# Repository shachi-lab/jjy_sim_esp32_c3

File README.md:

# 📡 JJY Simulator for ESP32-C3

電波時計の補正信号をESP32-C3で自作！
NTPから取得した正確な時刻をもとに、40kHz / 60kHz のJJY信号をPWM出力で模倣する、ミニJJYシミュレーターです。

## 🛠 特徴

- ESP32-C3 + Arduino によるコンパクトな構成
- Wi-Fi設定はボタンひとつで簡単APモード
- OLEDに現在時刻を表示
- PWM出力は GPIO10 から
- JJY 40kHz（東日本）/ 60kHz（西日本）を切り替え可能
- 出力信号は基板内蔵の簡易アンテナから放射

<br/>

## ⚙️ 使用方法

### 1. コンパイル・書き込み

1. Arduino IDE で ESP32ボードを有効にする  
   - ボードマネージャURL：`https://dl.espressif.com/dl/package_esp32_index.json`
   - 対象ボード：**ESP32-C3 Dev Module**

2. 必要なライブラリをインストールする  
   - [WiFiManager](https://github.com/tzapu/WiFiManager)（バージョン 2.0.17 推奨）
   - [ESP8266 and ESP32 OLED driver for SSD1306 displays](https://github.com/ThingPulse/esp8266-oled-ssd1306)（バージョン 4.6.0 推奨）

   ※ Arduino IDE の「ライブラリを管理」メニューからインストール可能です。

3. `JJY_Sim_ESP32_C3.ino` を開き、必要に応じて以下を編集：
   - `#define JJY_TYPE 0` → `0: 40kHz`, `1: 60kHz`

4. 書き込みポートとボード設定を確認して、コンパイル＆アップロード

> 💡 補足：
> ESP32-C3は、外付けのUSBシリアルICを使わず、チップ内蔵の**ネイティブUSB-UART**機能で書き込み・シリアル通信を行います。
> 一部の環境（特にWindows）では、デバイス認識のために**Espressif提供のUSBドライバ**が必要になる場合があります。

- ドライバDLページ 👉 https://www.espressif.com/en/support/download/other-tools

>⚠️ 初回起動について
> プログラムを書き込んだ直後の「初回起動」では、内部FLASHにファイルシステムを構築する処理が行われます。  
> このため、数十秒ほど反応がなく「ハングしたように見える」場合があります。  
> 完了すると自動的に再起動し、以降は通常通りすぐに動作しますが、再起動しない場合は、RESETボタンでリセットしてください。

### 2. Wi-Fi設定

- 電源投入 or リセット後、5秒以内に CONFIGスイッチを押す
- `ESP32_XXXXXXXX` というAPが起動（パスキー：`password`）
- スマホやPCから接続 → キャプティブポータルでSSID/パスキーを設定

### 3. 動作確認

- 電源投入 or リセット後、5秒間放置すると、WiFiのAPに接続しに行きます。
- APに接続すると、NTPサーバーから時刻を取得します。
- OLEDに現在時刻が表示され、0秒からPWMでJJY信号出力開始
- 電波時計の「受信ボタン」を押して、近くに置いておくだけ！

## 🔌 ピンアサイン（主なもの）

| 機能 | GPIO | 備考 |
|------|------|------|
| JJY PWM出力 | 10 | 変調された信号を出力 |
| CONFIGスイッチ | 9 | Wi-Fi設定用（**BOOTピンと兼用**） |
| ACT LED | 5 | 動作中LED |
| IND LED | 0 | 状態表示用LED（共用可） |
| OLED Reset | 2 | OLEDモジュールリセット |
| OLED SDA|7| OLED I2C データー|
| OLED SCL |6|OLED I2C クロック|

## 🧾 ファイル構成

```
JJY_Sim_ESP32_C3.ino       // メインスケッチ
wire_compat.h              // ESP32-C3 用の I2C バス互換ヘッダ
```

## 📎 依存ライブラリ

- [WiFiManager](https://github.com/tzapu/WiFiManager)
- [ESP8266 and ESP32 OLED driver](https://github.com/ThingPulse/esp8266-oled-ssd1306)

## 🔗 関連リンク

- ブログ記事（詳細解説＋ケースや基板配布）  
  👉 https://blog.shachi-lab.com/033_jjy_simulator/

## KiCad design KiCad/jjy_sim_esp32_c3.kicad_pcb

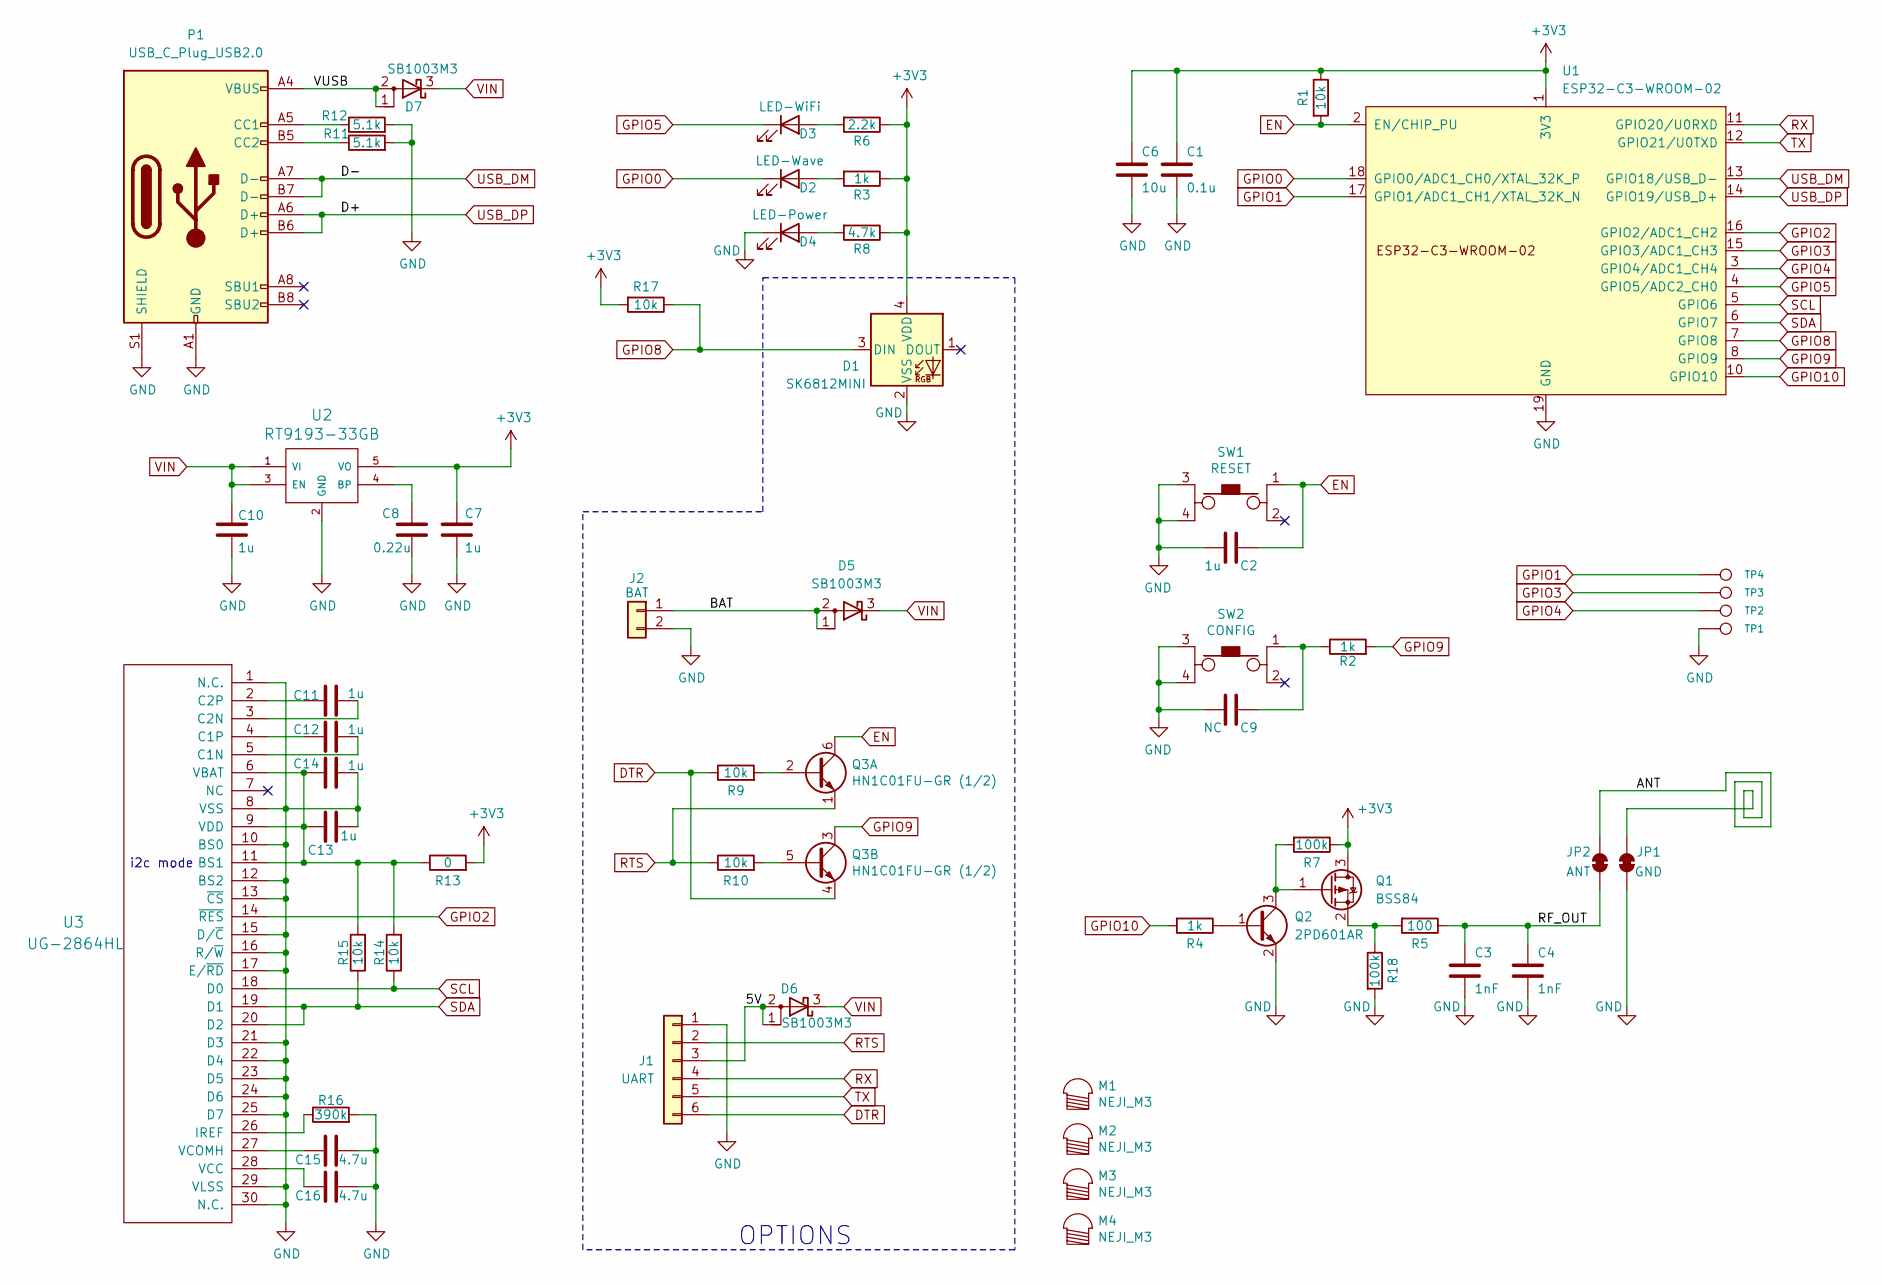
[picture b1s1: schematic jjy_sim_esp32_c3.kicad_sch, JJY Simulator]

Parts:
C1: 0.1u; C_0603_1608Metric
C2, C7, C10, C11, C12, C13, C14: 1u; C_0603_1608Metric
C3, C4: 1nF; C_0603_1608Metric
C6: 10u; C_0603_1608Metric
C8: 0.22u; C_0603_1608Metric
C9: NC; C_0603_1608Metric
C15, C16: 4.7u; C_0603_1608Metric
D1: SK6812MINI; LED_SK6812MINI_PLCC4_3.5x3.5mm_P1.75mm
D2: LED-Wave; LED_0603_1608Metric
D3: LED-WiFi; LED_0603_1608Metric
D4: LED-Power; LED_0603_1608Metric
D5, D6, D7: SB1003M3; SOT-323_SC-70
J1: UART; PinHeader_1x06_P2.54mm_Horizontal
J2: BAT; JST_PH_B2B-PH-K_1x02_P2.00mm_Vertical
JP1: GND; Jumper-2_TH_3.81mm
JP2: ANT; Jumper-2_TH_3.81mm
M1, M2, M3, M4: NEJI_M3; HOLE-3M_55
P1: USB_C_Plug_USB2.0; 5077CR-16SMC2-BK-TR
Q1: BSS84; SOT-23
Q2: 2PD601AR; SC-59
Q3: HN1C01FU-GR (1/2); 2-2J1A
R1, R9, R10, R14, R15, R17: 10k; R_0603_1608Metric
R2, R3, R4: 1k; R_0603_1608Metric
R5: 100; R_0603_1608Metric
R6: 2.2k; R_0603_1608Metric
R7, R18: 100k; R_0603_1608Metric
R8: 4.7k; R_0603_1608Metric
R11, R12: 5.1k; R_0603_1608Metric
R13: 0; R_0603_1608Metric
R16: 390k; R_0603_1608Metric
SW1: RESET; SKRPACE010
SW2: CONFIG; SKRPACE010
TP1, TP2, TP3, TP4: TP; TestPoint_THTPad_D1.5mm_Drill0.7mm
U1: ESP32-C3-WROOM-02
U2: RT9193-33GB; SOT-23-5
U3: UG-2864HL; UG-2864-FPC

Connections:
+3V3: C1.1, C6.1, C7.1, D1.4 (VDD), Q1.3 (D), R1.1, R3.1, R6.1, R7.1, R8.1, R13.2, R17.2, U1.1 (3V3), U2.5 (VO)
/5V: D6.1 (A), D6.2 (A), J1.3
/ANT: JP1.2 (B), JP2.2 (B)
/BAT: D5.1 (A), D5.2 (A), J2.1
/RF_OUT: C3.1, C4.1, JP2.1 (A), R5.1
/VUSB: D7.1 (A), D7.2 (A), P1.A4 (VBUS), P1.A9 (VBUS), P1.B4 (VBUS), P1.B9 (VBUS)
DTR: J1.6, Q3.4 (E2), R9.1
EN: C2.2, Q3.6 (C1), R1.2, SW1.1, U1.2 (EN/CHIP_PU)
GND: C1.2, C2.1, C3.2, C4.2, C6.2, C7.2, C8.2, C9.1, C10.2, C13.2, C14.2, C15.2, C16.2, D1.2 (VSS), D4.1 (K), J1.1, J2.2, JP1.1 (A), P1.A1 (GND), P1.A12 (GND), P1.B1 (GND), P1.B12 (GND), P1.S1 (SHIELD), Q2.2 (E), R11.2, R12.2, R16.2, R18.2, SW1.3, SW1.4, SW2.3, SW2.4, TP1.1, U1.9 (GND), U1.19 (GND), U2.2 (GND), U3.1 (N.C.), U3.8 (VSS), U3.10 (BS0), U3.12 (BS2), U3.13 (~CS), U3.15 (D/~C), U3.16 (R/~W), U3.17 (E/~RD), U3.21 (D3), U3.22 (D4), U3.23 (D5), U3.24 (D6), U3.25 (D7), U3.29 (VLSS), U3.30 (N.C.)
GPIO0: D2.1 (K), U1.18 (GPIO0/ADC1_CH0/XTAL_32K_P)
GPIO1: TP4.1, U1.17 (GPIO1/ADC1_CH1/XTAL_32K_N)
GPIO2: U1.16 (GPIO2/ADC1_CH2), U3.14 (~RES)
GPIO3: TP3.1, U1.15 (GPIO3/ADC1_CH3)
GPIO4: TP2.1, U1.3 (GPIO4/ADC1_CH4)
GPIO5: D3.1 (K), U1.4 (GPIO5/ADC2_CH0)
GPIO8: D1.3 (DIN), R17.1, U1.7 (GPIO8)
GPIO9: Q3.3 (C2), R2.2, U1.8 (GPIO9)
GPIO10: R4.2, U1.10 (GPIO10)
unnamed: C9.2, R2.1, SW2.1
unnamed: D2.2 (A), R3.2
unnamed: D3.2 (A), R6.2
unnamed: D4.2 (A), R8.2
unnamed: P1.A5 (CC1), R12.1
unnamed: P1.B5 (CC2), R11.1
unnamed: Q1.1 (G), Q2.3 (C), R7.2
unnamed: Q1.2 (S), R5.2, R18.1
unnamed: Q2.1 (B), R4.1
unnamed: Q3.2 (B1), R9.2
unnamed: Q3.5 (B2), R10.2
unnamed: C8.1, U2.4 (BP)
unnamed: C13.1, C14.1, R13.1, R14.2, R15.2, U3.6 (VBAT), U3.9 (VDD), U3.11 (BS1)
unnamed: C12.2, U3.5 (C1N)
unnamed: C12.1, U3.4 (C1P)
unnamed: C11.2, U3.3 (C2N)
unnamed: C11.1, U3.2 (C2P)
unnamed: R16.1, U3.26 (IREF)
unnamed: C16.1, U3.28 (VCC)
unnamed: C15.1, U3.27 (VCOMH)
RTS: J1.2, Q3.1 (E1), R10.1
RX: J1.4, U1.11 (GPIO20/U0RXD)
SCL: R14.1, U1.5 (GPIO6), U3.18 (D0)
SDA: R15.1, U1.6 (GPIO7), U3.19 (D1), U3.20 (D2)
TX: J1.5, U1.12 (GPIO21/U0TXD)
USB_DM: P1.A7 (D-), P1.B7 (D-), U1.13 (GPIO18/USB_D-)
USB_DP: P1.A6 (D+), P1.B6 (D+), U1.14 (GPIO19/USB_D+)
VIN: C10.1, D5.3 (K), D6.3 (K), D7.3 (K), U2.1 (VI), U2.3 (EN)

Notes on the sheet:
OPTIONS
i2c mode

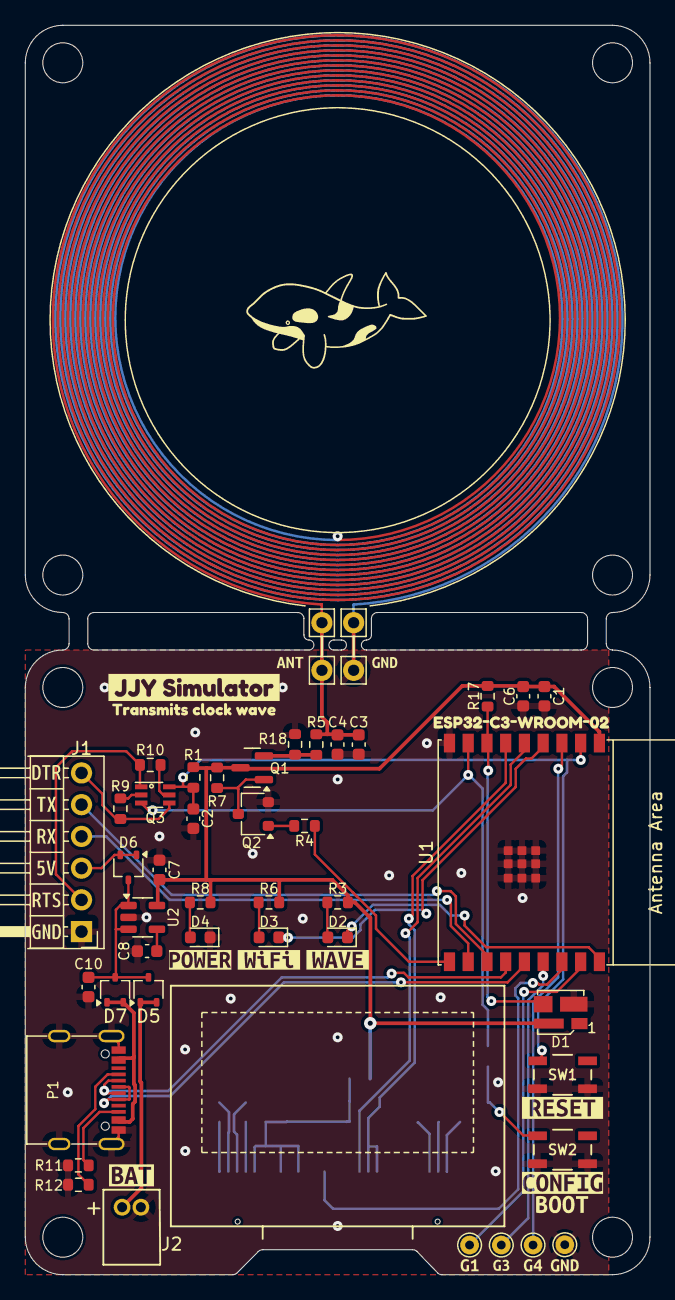
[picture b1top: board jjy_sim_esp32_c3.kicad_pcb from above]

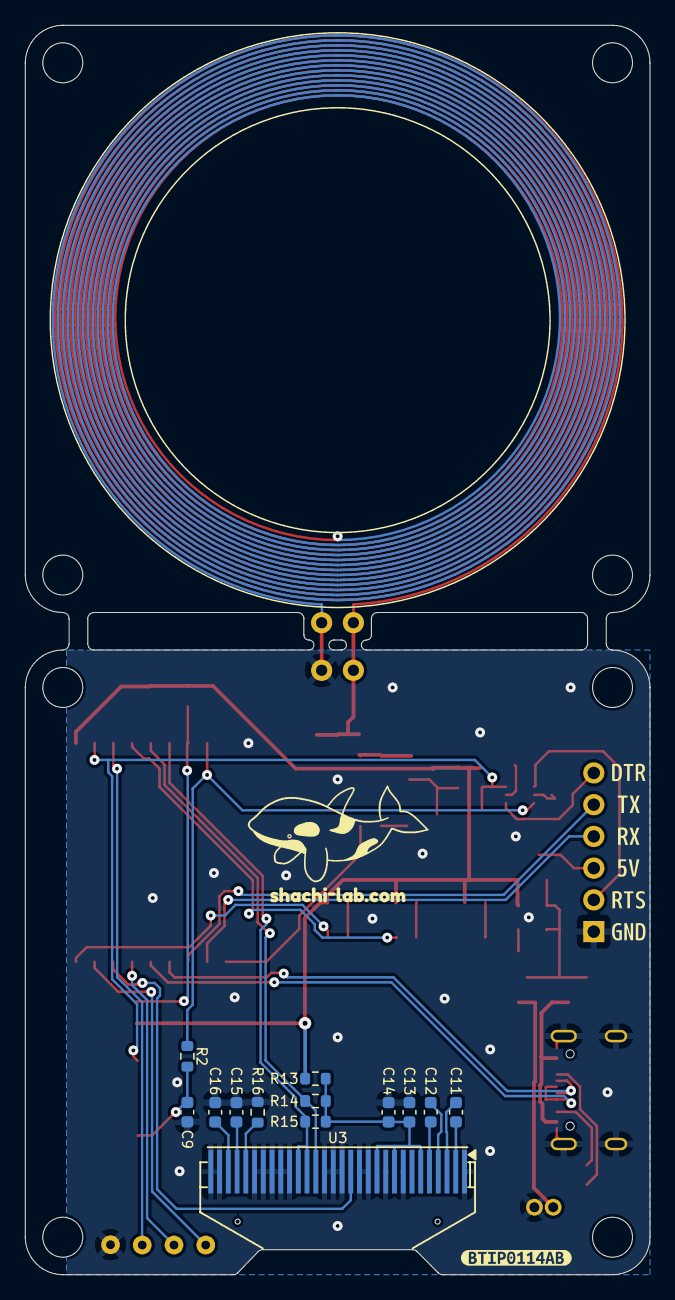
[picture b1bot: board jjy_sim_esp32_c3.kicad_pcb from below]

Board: 2 copper layers, 50.0 x 100.0 mm, 91 parts (21 on the bottom side), 46 nets.

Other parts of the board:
kibuzzard-5: G***; kibuzzard-665A8DD6
kibuzzard-7: G***; kibuzzard-664968E2
kibuzzard-9: G***; kibuzzard-6646C6AC
kibuzzard-13: G***; kibuzzard-6649687C
kibuzzard-665ABDD7: G***; kibuzzard-665ABDD7
kibuzzard-665AC270: G***; kibuzzard-665AC270
kibuzzard-665B35A8: G***; kibuzzard-665B35A8
kibuzzard-665B35AE: G***; kibuzzard-665B35AE
kibuzzard-665B35C9: G***; kibuzzard-665B35C9
kibuzzard-665B357F: G***; kibuzzard-665B357F
kibuzzard-665B3587: G***; kibuzzard-665B3587
kibuzzard-665BB8A3: G***; kibuzzard-665BB8A3
kibuzzard-665BB8AA: G***; kibuzzard-665BB8AA
kibuzzard-665BB8B1: G***; kibuzzard-665BB8B1
kibuzzard-665BB88E: G***; kibuzzard-665BB88E
kibuzzard-665BB89D: G***; kibuzzard-665BB89D
kibuzzard-665BBA5E: G***; kibuzzard-665BBA5E
kibuzzard-665BBA6E: G***; kibuzzard-665BBA6E
kibuzzard-665BBA64: G***; kibuzzard-665BBA64
kibuzzard-665BBA69: G***; kibuzzard-665BBA69
kibuzzard-665BBA79: G***; kibuzzard-665BBA79
kibuzzard-667C13C8: G***; kibuzzard-667C13C8
kibuzzard-669B6BC9: G***; kibuzzard-669B6BC9
kibuzzard-669B6D24: G***; kibuzzard-669B6D24
kibuzzard-669B6DC4: G***; kibuzzard-669B6DC4
kibuzzard-669B16B9: G***; kibuzzard-669B16B9
kibuzzard-669B4532: G***; kibuzzard-669B4532
kibuzzard-669B8430: G***; kibuzzard-669B8430
kibuzzard-669B8438: G***; kibuzzard-669B8438
kibuzzard-66603A24: G***; kibuzzard-66603A24

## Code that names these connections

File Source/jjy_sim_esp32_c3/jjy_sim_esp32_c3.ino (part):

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
#define JST               (9*3600)
#undef  BUILTIN_LED
#define BUILTIN_LED       0       // GPIO0
#define IND_LED           BUILTIN_LED
#define ACT_LED           5       // GPIO5
#define LED_ON            0
#define LED_OFF           1
#define LED_BLINK         2

#define CONFIG_PIN        9       // GPIO9
#define OLED_RES_PIN      2       // GPIO2
#define PWM_PIN           10      // GPIO10
#define SCL               6       // GPIO6
#define SDA               7       // GPIO5

#define I2CADR            0x3c

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
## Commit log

2025-08-13 1st commit
2025-08-13 README修正
2025-08-20 C3,C4定数変更、C5をR18に変更
2025-08-21 READMEに、初回起動時の注意事項を追加
